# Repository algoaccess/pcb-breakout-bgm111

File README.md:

# pcb-breakout-bgm111
Pin breakout of the Silicon Labs BGM111 module to through-hole pin headers for prototyping.

##PCB Design software and addons used

1. Eagle 7.3.0: I use Standard but Light should still be able to open/modify the files.
2. BGM111 library by [jshrowberg](https://github.com/jrowberg/sf-oshw/tree/master/bluegiga/eagle) (in repo as sf-bluegiga.lbr)

##Images
None at this time

##Schematic drawings
Images are exported from Eagle at 600dpi.

##Parts required

The BGM111 module can be bought from one of the online stores like [Mouser](http://www.mouser.sg/new/Silicon-Laboratories/silabs-bgm111-module/)

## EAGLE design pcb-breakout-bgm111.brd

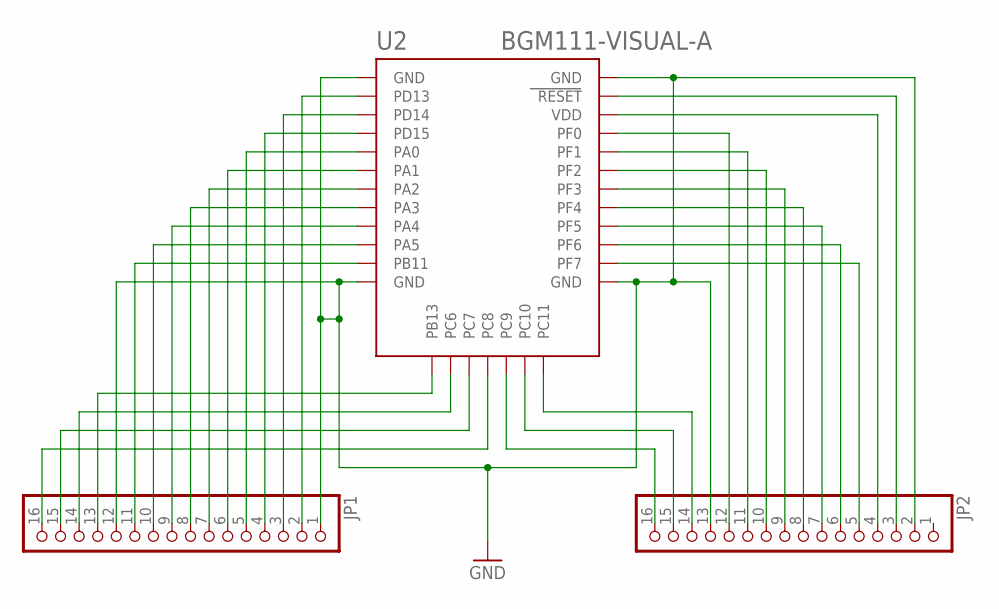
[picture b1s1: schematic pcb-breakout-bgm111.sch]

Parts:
JP1, JP2: PINHD-1X16; 1X16
U2: BGM111-VISUAL-A; BGM111-A

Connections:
GND: JP1.1, JP1.12, JP2.2, JP2.13, U2.GND, U2.GND@2 (GND), U2.GND@3 (GND), U2.GND@4 (GND)
unnamed: JP1.2, U2.PD13
unnamed: JP1.3, U2.PD14
unnamed: JP1.4, U2.PD15
unnamed: JP1.5, U2.PA0
unnamed: JP1.6, U2.PA1
unnamed: JP1.7, U2.PA2
unnamed: JP1.8, U2.PA3
unnamed: JP1.9, U2.PA4
unnamed: JP1.10, U2.PA5
unnamed: JP1.11, U2.PB11
unnamed: JP1.13, U2.PB13
unnamed: JP1.14, U2.PC6
unnamed: JP1.15, U2.PC7
unnamed: JP1.16, U2.PC8
unnamed: JP2.16, U2.PC9
unnamed: JP2.15, U2.PC10
unnamed: JP2.14, U2.PC11
unnamed: JP2.3, U2.RESET
unnamed: JP2.4, U2.VDD
unnamed: JP2.5, U2.PF7
unnamed: JP2.6, U2.PF6
unnamed: JP2.7, U2.PF5
unnamed: JP2.8, U2.PF4
unnamed: JP2.9, U2.PF3
unnamed: JP2.10, U2.PF2
unnamed: JP2.11, U2.PF1
unnamed: JP2.12, U2.PF0

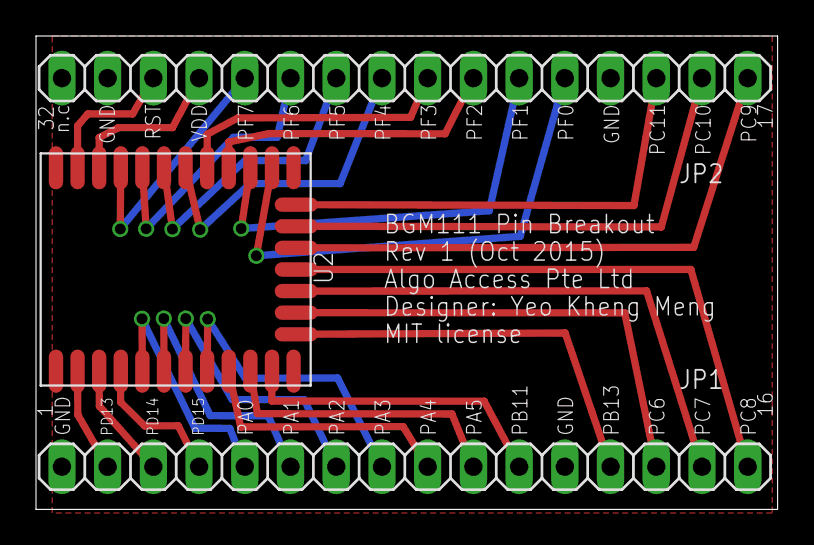
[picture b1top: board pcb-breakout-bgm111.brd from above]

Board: 2 copper layers, 41.2 x 26.3 mm, 3 parts (0 on the bottom side), 28 nets.

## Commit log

2015-10-20 pin labels
2015-10-20 pin numbering
2015-10-20 rev1 gerbel
2015-10-20 larger silkscreen
2015-10-27 permission
2015-10-27 images

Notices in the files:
pcb-breakout-bgm111.brd:
MIT license
